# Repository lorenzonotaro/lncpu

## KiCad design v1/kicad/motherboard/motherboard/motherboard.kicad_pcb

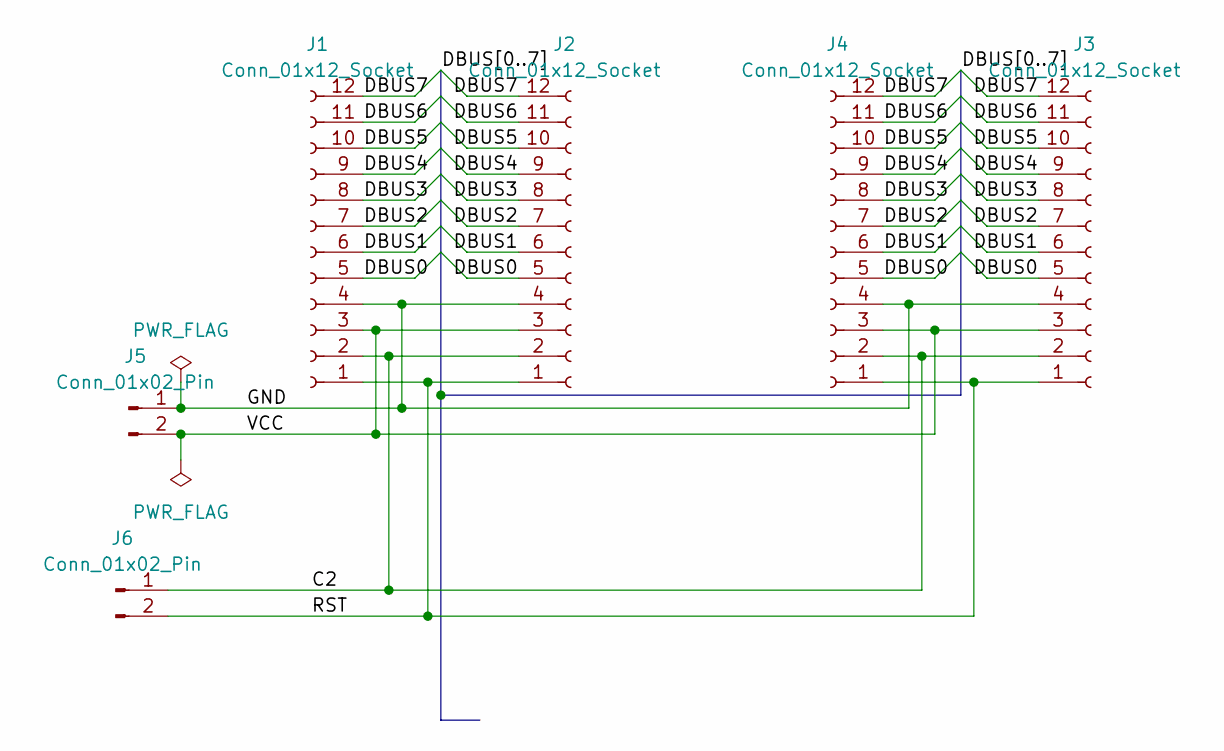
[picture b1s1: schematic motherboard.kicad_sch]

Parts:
J1, J2, J3, J4: Conn_01x12_Socket; PinSocket_1x12_P2.54mm_Vertical
J5, J6: Conn_01x02_Pin; PinSocket_1x02_P2.54mm_Vertical

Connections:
/C2: J1.2, J2.2, J3.2, J4.2, J6.1
/DBUS0: J1.5, J2.5, J3.5, J4.5
/DBUS1: J1.6, J2.6, J3.6, J4.6
/DBUS2: J1.7, J2.7, J3.7, J4.7
/DBUS3: J1.8, J2.8, J3.8, J4.8
/DBUS4: J1.9, J2.9, J3.9, J4.9
/DBUS5: J1.10, J2.10, J3.10, J4.10
/DBUS6: J1.11, J2.11, J3.11, J4.11
/DBUS7: J1.12, J2.12, J3.12, J4.12
/GND: J1.4, J2.4, J3.4, J4.4, J5.1
/VCC: J1.3, J2.3, J3.3, J4.3, J5.2
/~RESET: J1.1, J2.1, J3.1, J4.1, J6.2

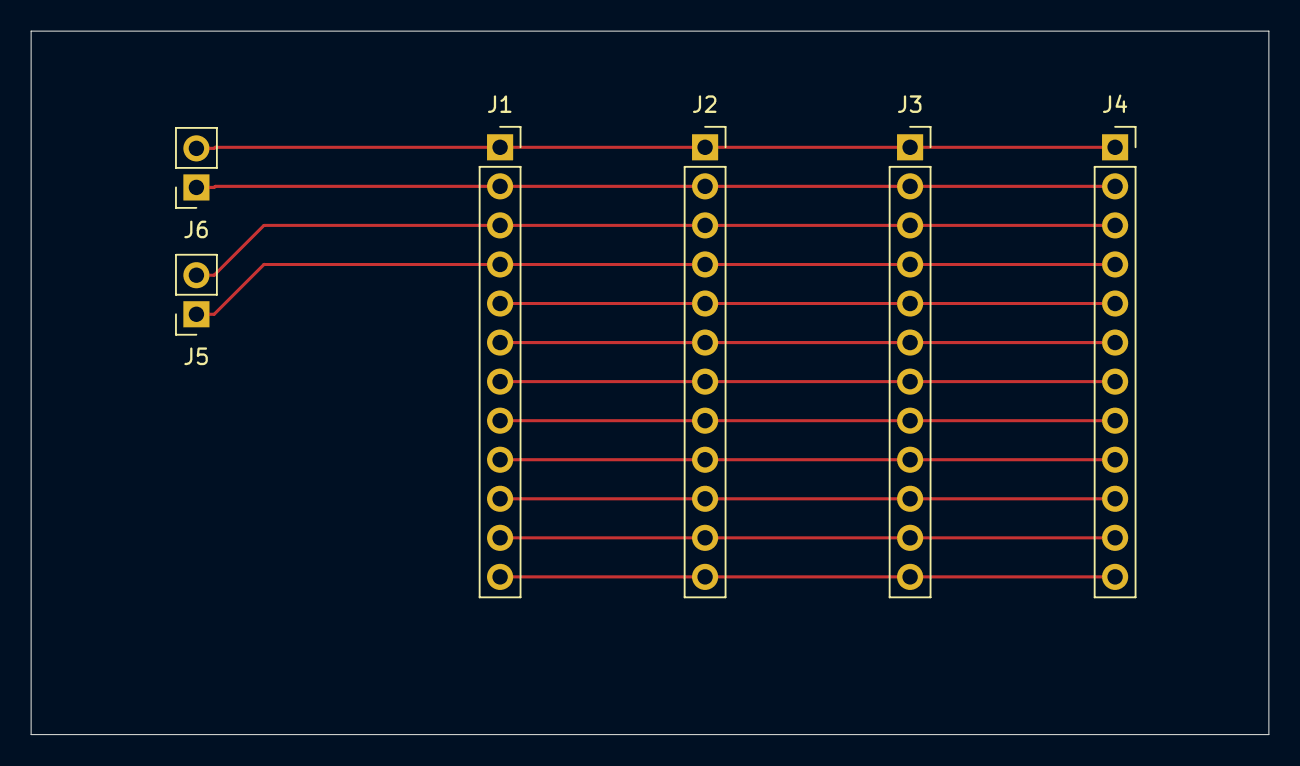
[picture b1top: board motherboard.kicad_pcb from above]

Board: 2 copper layers, 80.5 x 45.8 mm, 6 parts (0 on the bottom side), 12 nets.

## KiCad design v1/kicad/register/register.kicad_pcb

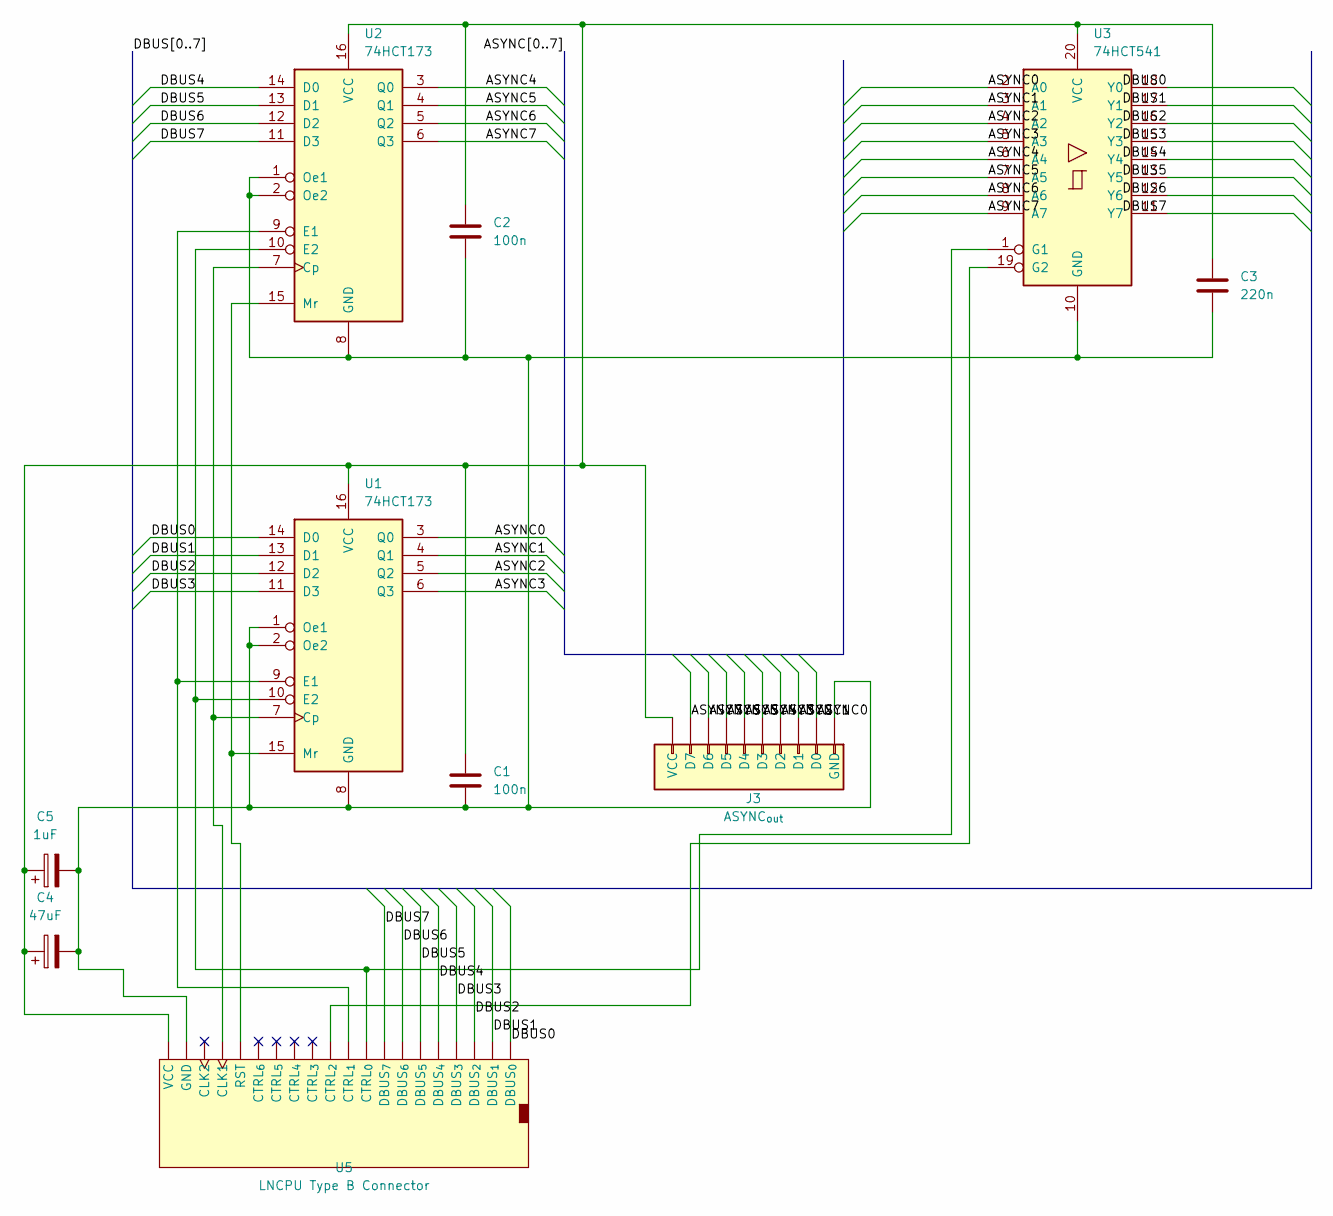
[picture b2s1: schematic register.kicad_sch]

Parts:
C1, C2: 100n; C_Disc_D4.3mm_W1.9mm_P5.00mm
C3: 220n; C_Disc_D4.3mm_W1.9mm_P5.00mm
C4: 47uF; CP_Radial_D5.0mm_P2.50mm
C5: 1uF; CP_Radial_D4.0mm_P2.00mm-Large-Holes
J3: ASYNC_{out}; PinSocket_1x10_P2.54mm_Vertical
U1, U2: 74HCT173; DIP-16_W7.62mm_LongPads
U3: 74HCT541; DIP-20_W7.62mm_LongPads
U5: LNCPU Type B Connector; LNCPU_Type_B_Header

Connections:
/ASYNC0: J3.2 (D0), U1.3 (Q0), U3.2 (A0)
/ASYNC1: J3.3 (D1), U1.4 (Q1), U3.3 (A1)
/ASYNC2: J3.4 (D2), U1.5 (Q2), U3.4 (A2)
/ASYNC3: J3.5 (D3), U1.6 (Q3), U3.5 (A3)
/ASYNC4: J3.6 (D4), U2.3 (Q0), U3.6 (A4)
/ASYNC5: J3.7 (D5), U2.4 (Q1), U3.7 (A5)
/ASYNC6: J3.8 (D6), U2.5 (Q2), U3.8 (A6)
/ASYNC7: J3.9 (D7), U2.6 (Q3), U3.9 (A7)
/DBUS0: U1.14 (D0), U3.18 (Y0), U5.3 (DBUS_{0})
/DBUS1: U1.13 (D1), U3.17 (Y1), U5.5 (DBUS_{1})
/DBUS2: U1.12 (D2), U3.16 (Y2), U5.7 (DBUS_{2})
/DBUS3: U1.11 (D3), U3.15 (Y3), U5.9 (DBUS_{3})
/DBUS4: U2.14 (D0), U3.14 (Y4), U5.11 (DBUS_{4})
/DBUS5: U2.13 (D1), U3.13 (Y5), U5.13 (DBUS_{5})
/DBUS6: U2.12 (D2), U3.12 (Y6), U5.15 (DBUS_{6})
/DBUS7: U2.11 (D3), U3.11 (Y7), U5.17 (DBUS_{7})
unnamed: C1.2, C2.2, C3.2, C4.2, C5.2, J3.1 (GND), U1.1 (Oe1), U1.2 (Oe2), U1.8 (GND), U2.1 (Oe1), U2.2 (Oe2), U2.8 (GND), U3.10 (GND), U5.1 (GND), U5.18 (GND), U5.22 (GND), U5.23 (GND)
unnamed: C1.1, C2.1, C3.1, C4.1, C5.1, J3.10 (VCC), U1.16 (VCC), U2.16 (VCC), U3.20 (VCC), U5.2 (VCC), U5.24 (VCC)
unnamed: U1.7 (Cp), U2.7 (Cp), U5.21 (CLK1)
unnamed: U1.9 (E1), U2.9 (E1), U5.6 (CTRL_{1})
unnamed: U1.10 (E2), U2.10 (E2), U3.1 (G1), U5.4 (CTRL_{0})
unnamed: U1.15 (Mr), U2.15 (Mr), U5.19 (RST)
unnamed: U3.19 (G2), U5.8 (CTRL_{2})

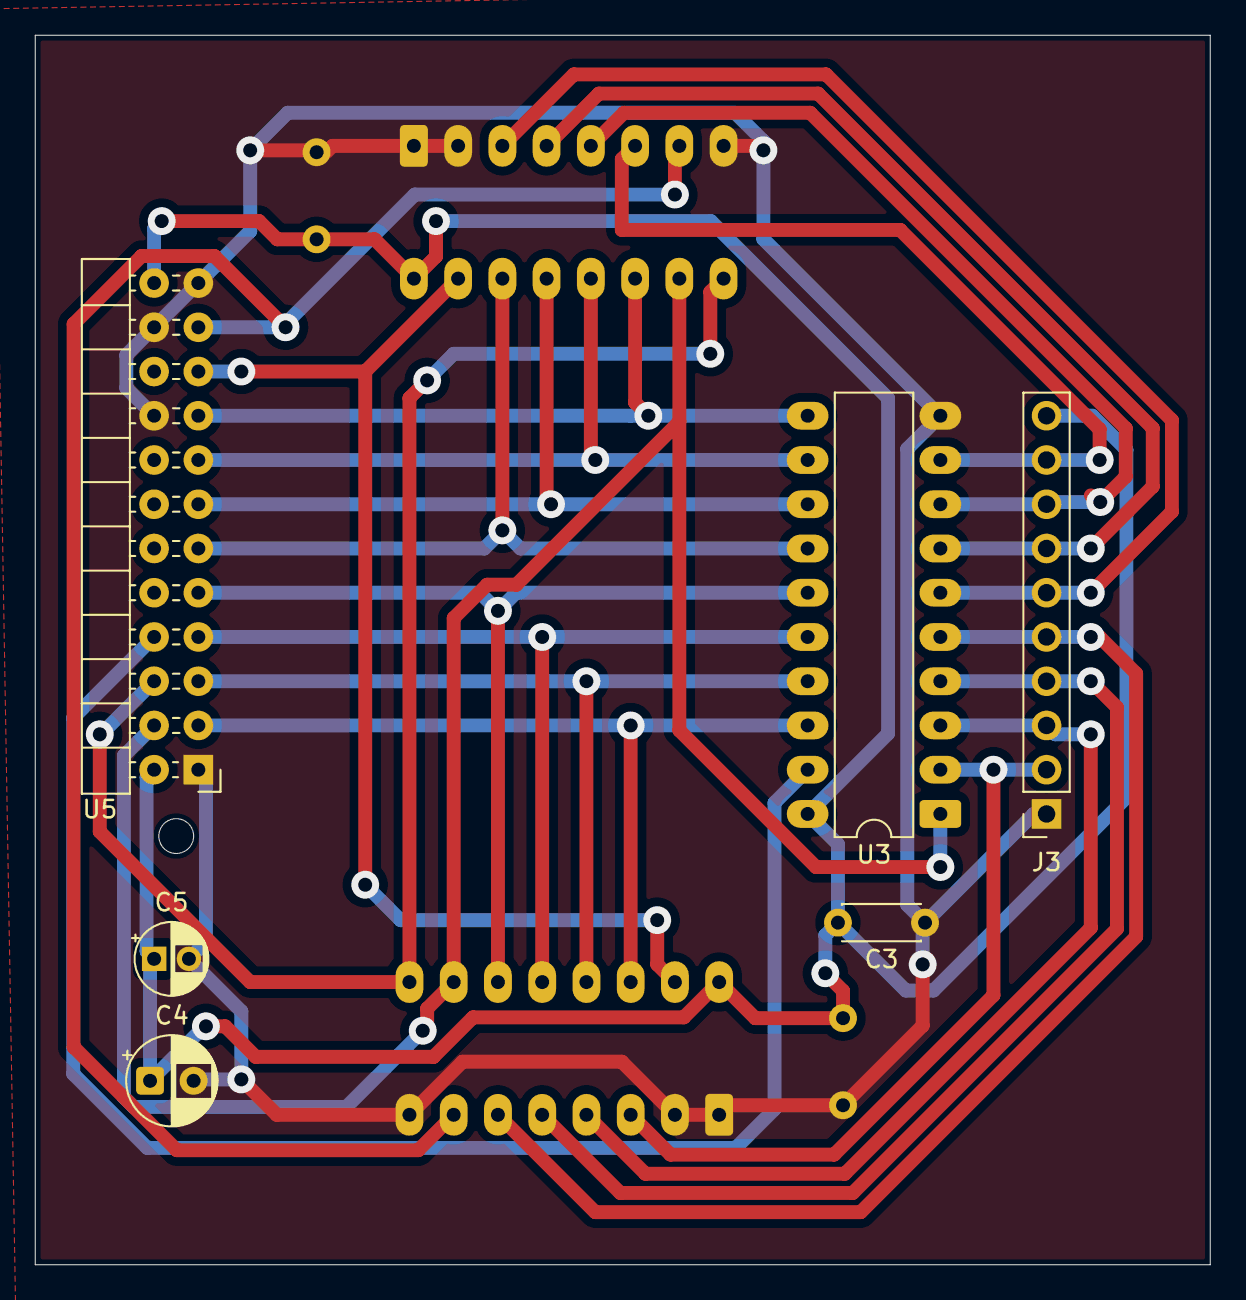
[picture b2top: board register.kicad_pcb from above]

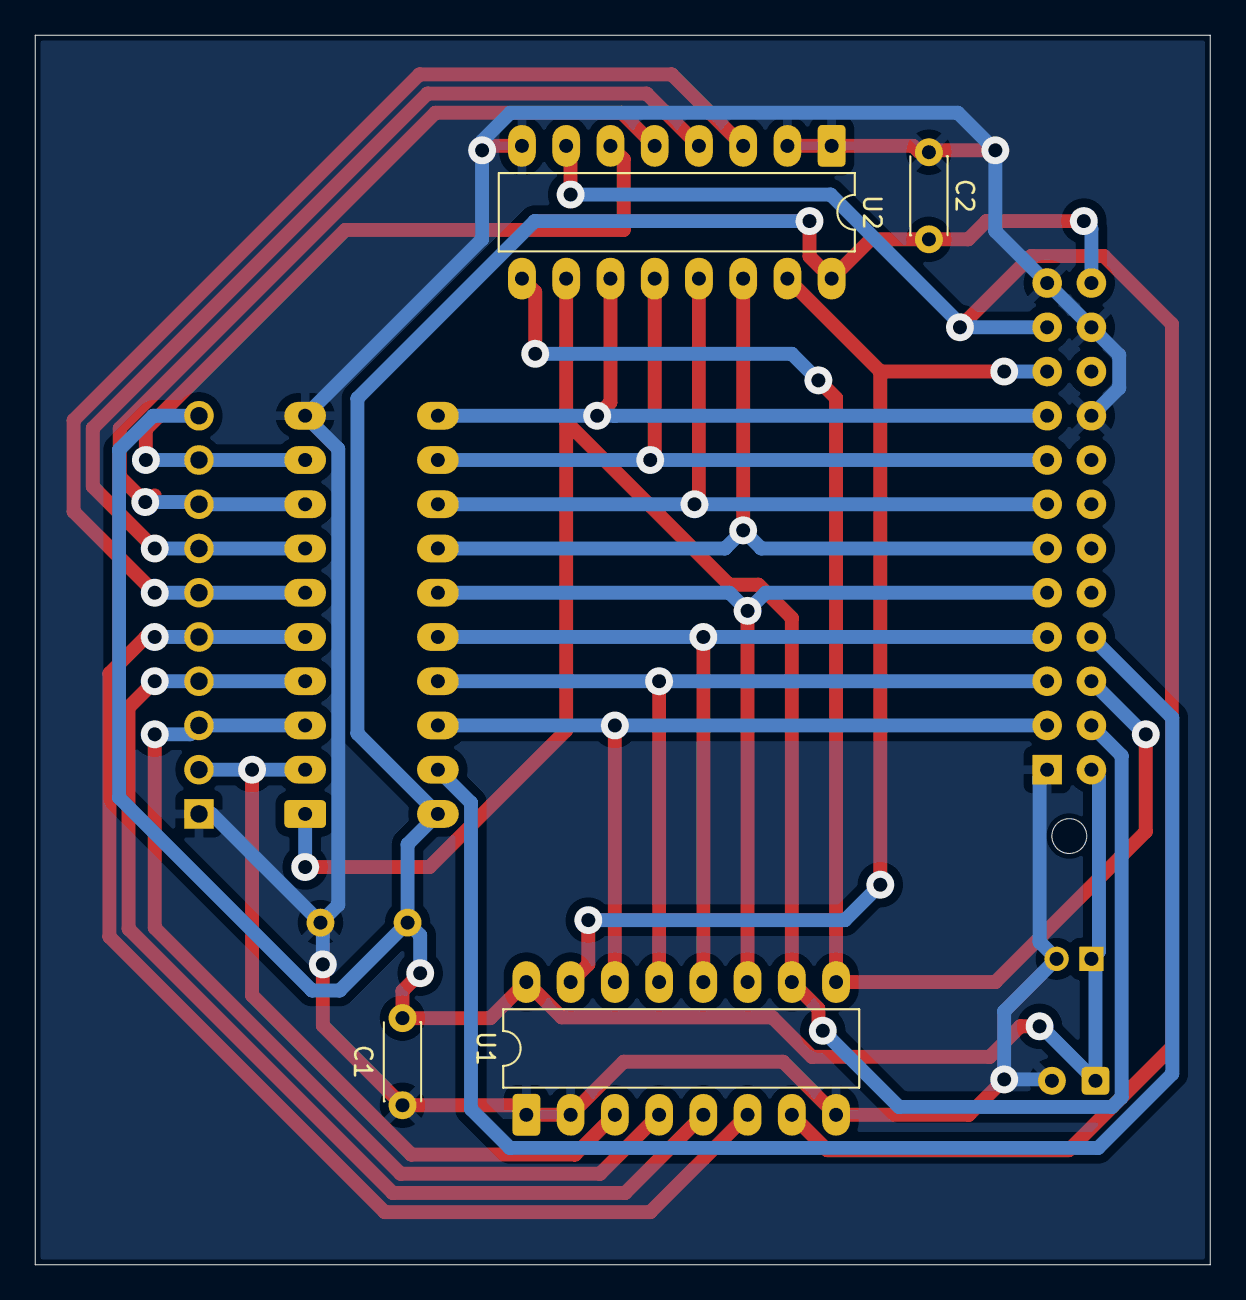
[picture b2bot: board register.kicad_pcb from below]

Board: 2 copper layers, 67.5 x 70.6 mm, 10 parts (4 on the bottom side), 23 nets.

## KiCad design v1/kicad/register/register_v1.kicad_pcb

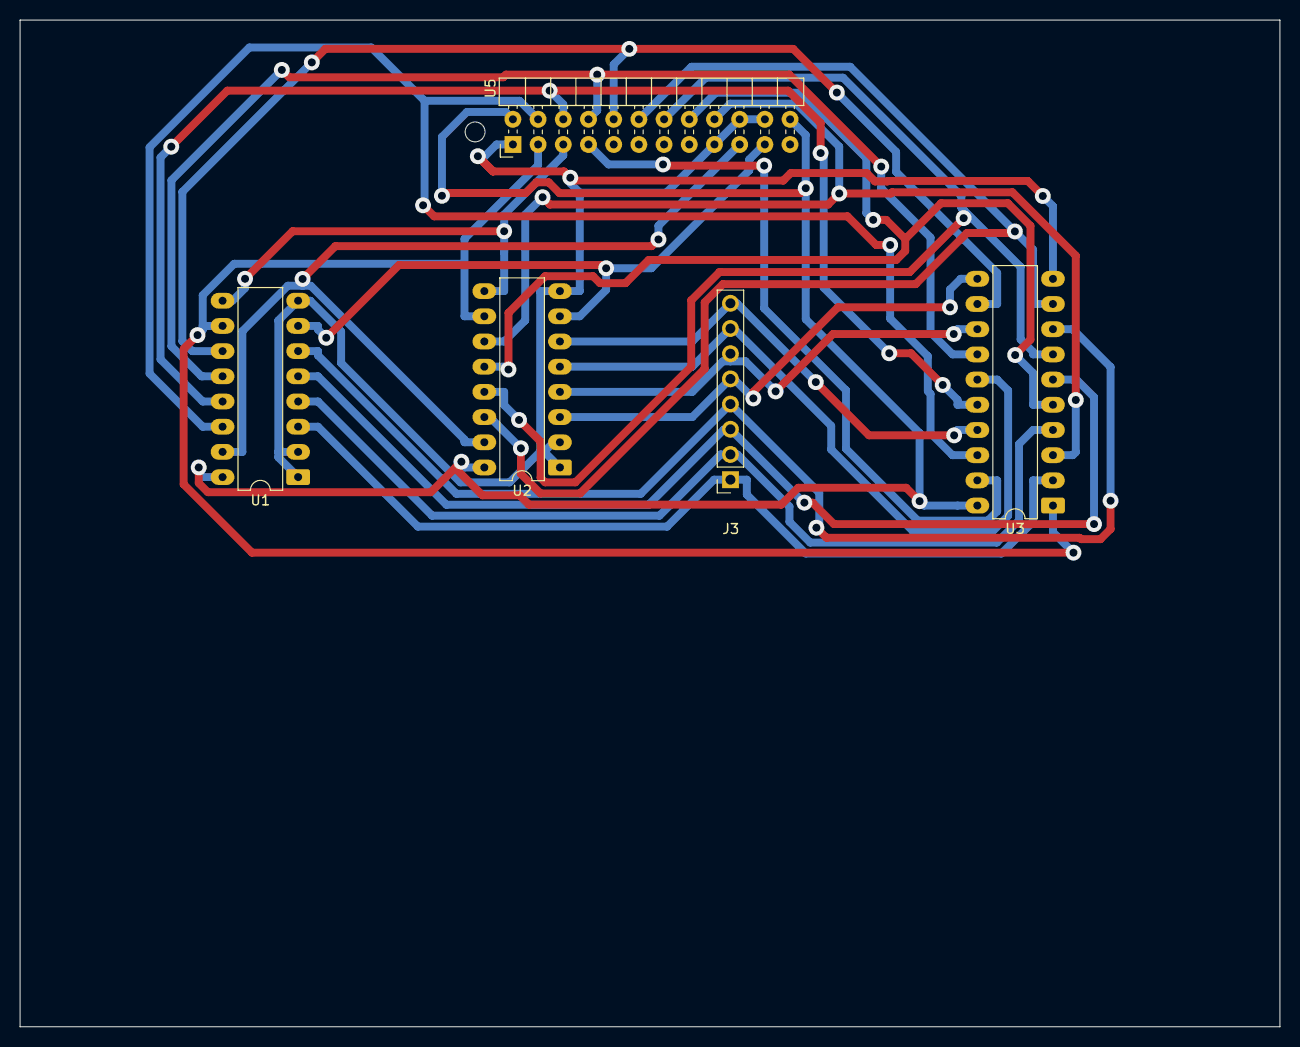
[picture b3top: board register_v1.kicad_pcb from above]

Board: 2 copper layers, 127.0 x 101.5 mm, 5 parts (0 on the bottom side), 23 nets.

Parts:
J3: ASYNC_{out}; PinSocket_1x08_P2.54mm_Vertical
U1, U2: 74HC173; DIP-16_W7.62mm_LongPads
U3: 74LS244; DIP-20_W7.62mm_LongPads
U5: LNCPU Type B Connector; LNCPU_Type_B_Header

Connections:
/ASYNC0: J3.1, U1.3 (Q0), U3.2 (I0a)
/ASYNC1: J3.2, U1.4 (Q1), U3.4 (I1a)
/ASYNC2: J3.3, U1.5 (Q2), U3.6 (I2a)
/ASYNC3: J3.4, U1.6 (Q3), U3.8 (I3a)
/ASYNC4: J3.5, U2.3 (Q0), U3.11 (I0b)
/ASYNC5: J3.6, U2.4 (Q1), U3.13 (I1b)
/ASYNC6: J3.7, U2.5 (Q2), U3.15 (I2b)
/ASYNC7: J3.8, U2.6 (Q3), U3.17 (I3b)
/DBUS0: U1.14 (D0), U3.18 (O0a), U5.4 (DBUS_{0})
/DBUS1: U1.13 (D1), U3.16 (O1a), U5.6 (DBUS_{1})
/DBUS2: U1.12 (D2), U3.14 (O2a), U5.8 (DBUS_{2})
/DBUS3: U1.11 (D3), U3.12 (O3a), U5.10 (DBUS_{3})
/DBUS4: U2.14 (D0), U3.9 (O0b), U5.12 (DBUS_{4})
/DBUS5: U2.13 (D1), U3.7 (O1b), U5.14 (DBUS_{5})
/DBUS6: U2.12 (D2), U3.5 (O2b), U5.16 (DBUS_{6})
/DBUS7: U2.11 (D3), U3.3 (O3b), U5.18 (DBUS_{7})
unnamed: U1.7 (Cp), U2.7 (Cp), U5.21 (CLK1)
unnamed: U1.9 (E1), U2.9 (E1), U5.5 (CTRL_{1})
unnamed: U1.10 (E2), U2.10 (E2), U3.1 (OEa), U5.3 (CTRL_{0})
unnamed: U1.1 (Oe1), U1.2 (Oe2), U1.8 (GND), U2.1 (Oe1), U2.2 (Oe2), U2.8 (GND), U3.10 (GND), U5.1 (GND), U5.17 (GND), U5.20 (GND), U5.22 (GND)
unnamed: U1.15 (Mr), U2.15 (Mr), U5.19 (RST)
unnamed: U1.16 (VCC), U2.16 (VCC), U3.20 (VCC), U5.2 (VCC), U5.24 (VCC)
unnamed: U3.19 (OEb), U5.7 (CTRL_{2})

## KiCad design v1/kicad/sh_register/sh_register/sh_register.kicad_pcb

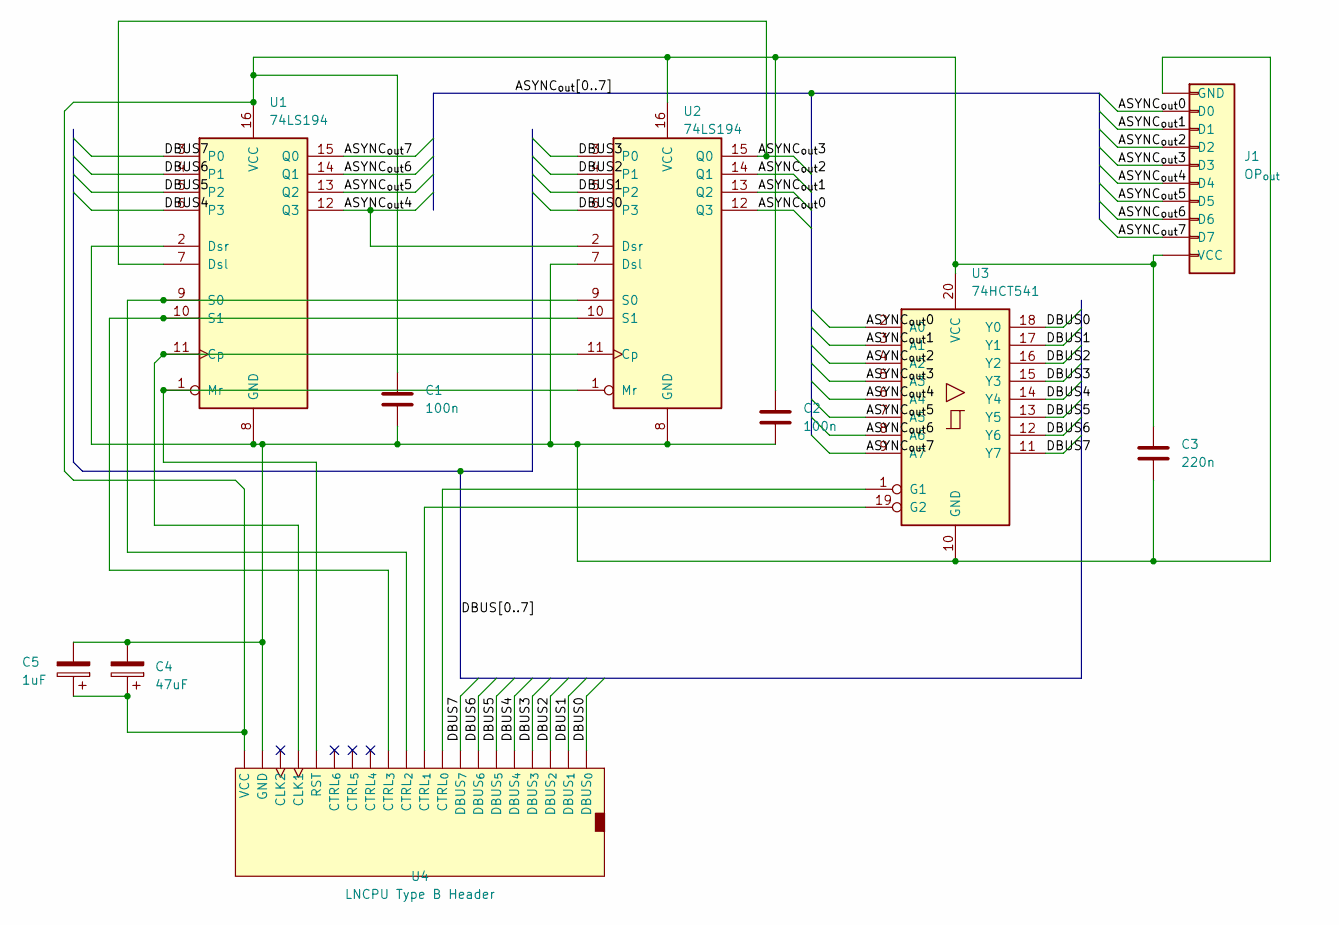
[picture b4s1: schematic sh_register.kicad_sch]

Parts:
C1, C2: 100n; C_Disc_D4.3mm_W1.9mm_P5.00mm
C3: 220n; C_Disc_D4.3mm_W1.9mm_P5.00mm
C4: 47uF; CP_Radial_D5.0mm_P2.00mm
C5: 1uF; CP_Radial_D4.0mm_P2.00mm-Large-Holes
J1: OP_{out}; PinSocket_1x10_P2.54mm_Vertical
U1, U2: 74LS194; DIP-16_W7.62mm_LongPads
U3: 74HCT541; DIP-20_W7.62mm_LongPads
U4: LNCPU Type B Header; LNCPU_Type_B_Header

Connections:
/ASYNC_{out}0: J1.2 (D0), U2.12 (Q3), U3.2 (A0)
/ASYNC_{out}1: J1.3 (D1), U2.13 (Q2), U3.3 (A1)
/ASYNC_{out}2: J1.4 (D2), U2.14 (Q1), U3.4 (A2)
/ASYNC_{out}3: J1.5 (D3), U1.7 (Dsl), U2.15 (Q0), U3.5 (A3)
/ASYNC_{out}4: J1.6 (D4), U1.12 (Q3), U2.2 (Dsr), U3.6 (A4)
/ASYNC_{out}5: J1.7 (D5), U1.13 (Q2), U3.7 (A5)
/ASYNC_{out}6: J1.8 (D6), U1.14 (Q1), U3.8 (A6)
/ASYNC_{out}7: J1.9 (D7), U1.15 (Q0), U3.9 (A7)
/DBUS0: U2.6 (P3), U3.18 (Y0), U4.3 (DBUS_{0})
/DBUS1: U2.5 (P2), U3.17 (Y1), U4.5 (DBUS_{1})
/DBUS2: U2.4 (P1), U3.16 (Y2), U4.7 (DBUS_{2})
/DBUS3: U2.3 (P0), U3.15 (Y3), U4.9 (DBUS_{3})
/DBUS4: U1.6 (P3), U3.14 (Y4), U4.11 (DBUS_{4})
/DBUS5: U1.5 (P2), U3.13 (Y5), U4.13 (DBUS_{5})
/DBUS6: U1.4 (P1), U3.12 (Y6), U4.15 (DBUS_{6})
/DBUS7: U1.3 (P0), U3.11 (Y7), U4.17 (DBUS_{7})
unnamed: C1.1, C2.1, C3.1, C4.1, C5.1, J1.10 (VCC), U1.16 (VCC), U2.16 (VCC), U3.20 (VCC), U4.2 (VCC), U4.24 (VCC)
unnamed: U1.11 (Cp), U2.11 (Cp), U4.21 (CLK1)
unnamed: C1.2, C2.2, C3.2, C4.2, C5.2, J1.1 (GND), U1.2 (Dsr), U1.8 (GND), U2.7 (Dsl), U2.8 (GND), U3.10 (GND), U4.1 (GND), U4.18 (GND), U4.22 (GND), U4.23 (GND)
unnamed: U1.1 (Mr), U2.1 (Mr), U4.19 (RST)
unnamed: U1.9 (S0), U2.9 (S0), U4.8 (CTRL_{2})
unnamed: U1.10 (S1), U2.10 (S1), U4.10 (CTRL_{3})
unnamed: U3.1 (G1), U4.4 (CTRL_{0})
unnamed: U3.19 (G2), U4.6 (CTRL_{1})

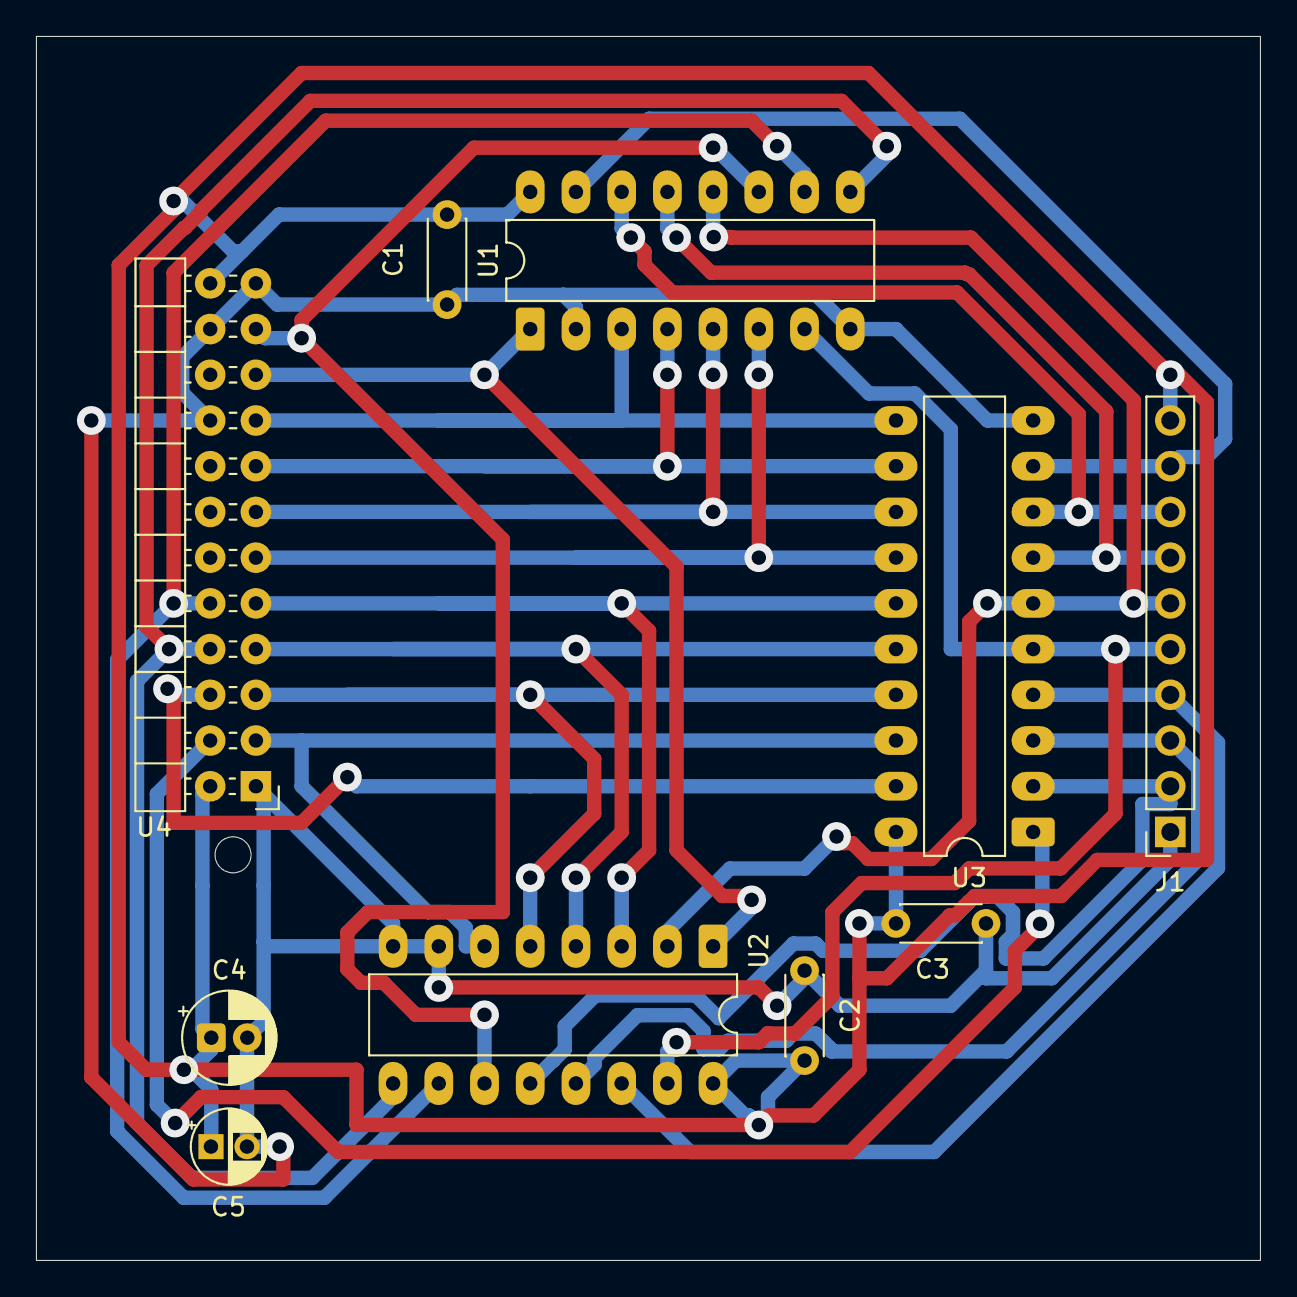
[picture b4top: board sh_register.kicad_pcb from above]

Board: 2 copper layers, 68.0 x 68.0 mm, 10 parts (0 on the bottom side), 24 nets.

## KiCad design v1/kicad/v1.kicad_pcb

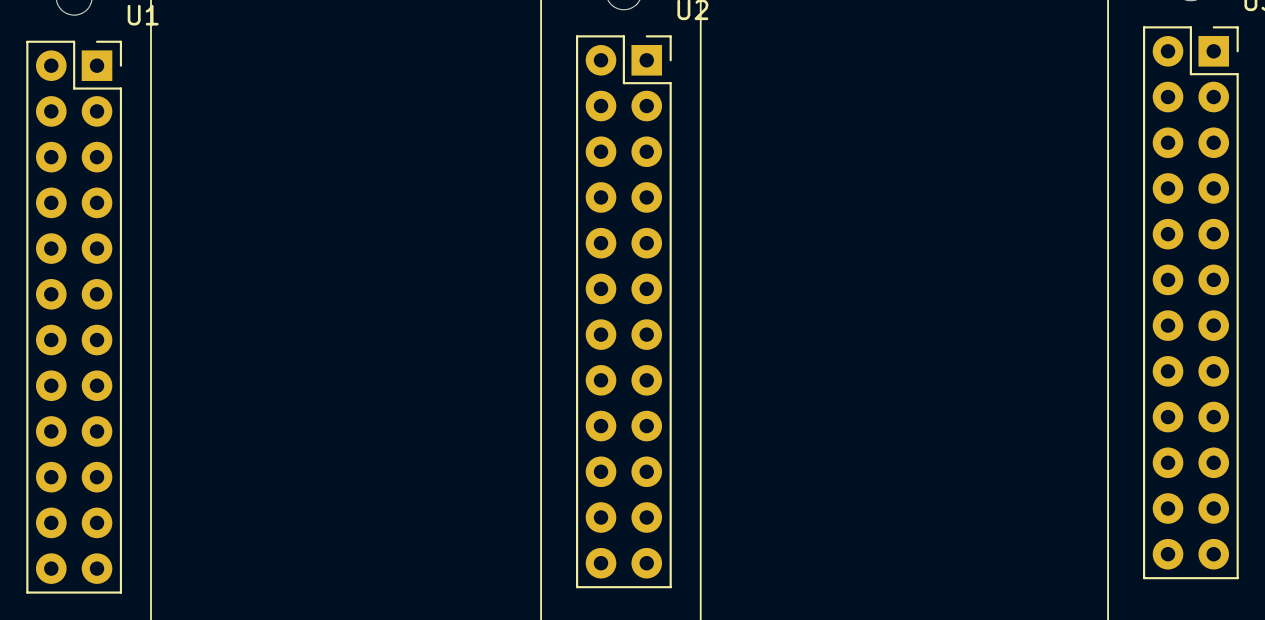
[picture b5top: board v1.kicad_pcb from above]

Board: 2 copper layers, 3 parts (0 on the bottom side), 12 nets, no tracks yet.

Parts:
U1: RB; LNCPU_GP_Register
U2: RC; LNCPU_GP_Register
U3: RD; LNCPU_GP_Register

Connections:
DBUS0: U1.4 (DBUS_{0}), U2.4 (DBUS_{0}), U3.4 (DBUS_{0})
DBUS1: U1.6 (DBUS_{1}), U2.6 (DBUS_{1}), U3.6 (DBUS_{1})
DBUS2: U1.8 (DBUS_{2}), U2.8 (DBUS_{2}), U3.8 (DBUS_{2})
DBUS3: U1.10 (DBUS_{3}), U2.10 (DBUS_{3}), U3.10 (DBUS_{3})
DBUS4: U1.12 (DBUS_{4}), U2.12 (DBUS_{4}), U3.12 (DBUS_{4})
DBUS5: U1.14 (DBUS_{5}), U2.14 (DBUS_{5}), U3.14 (DBUS_{5})
DBUS6: U1.16 (DBUS_{6}), U2.16 (DBUS_{6}), U3.16 (DBUS_{6})
DBUS7: U1.18 (DBUS_{7}), U2.18 (DBUS_{7}), U3.18 (DBUS_{7})
GND: U1.1 (GND), U1.17 (GND), U1.20 (GND), U1.22 (GND), U2.1 (GND), U2.17 (GND), U2.20 (GND), U2.22 (GND), U3.1 (GND), U3.17 (GND), U3.20 (GND), U3.22 (GND)
PHI_{2}: U1.3 (~R_{en}), U2.3 (~R_{en}), U3.3 (~R_{en})
RST: U1.19 (RST), U2.19 (RST), U3.19 (RST)
VCC: U1.2 (VCC), U1.24 (VCC), U2.2 (VCC), U2.24 (VCC), U3.2 (VCC), U3.24 (VCC)
